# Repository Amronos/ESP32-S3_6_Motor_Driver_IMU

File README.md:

# ESP32-S3 6 Motor Driver with IMU

**_This board is currently in development._**

This board features an **ESP32-S3** microcontroller, a **6-channel** DC **motor driver**, and an integrated **BNO086 IMU** for precise motion and orientation data.<br>
It supports **encoder feedback**, enabling accurate position control. Motors can be driven at voltages up to **36V**.

This board is perfect for robots requiring more than two motors.<br>
Simply wire your motors, connect the board to a PC, another microcontroller, or even your phone/tablet and use the ESP32-S3's versatile communication options like I2C, SPI, UART, Wi-Fi, and Bluetooth to control your robot.

A full **Arduino library** for the board is available that allows you to control the motors, IMU, and read data from the encoders.<br>
Sample **ROS 2** packages are also available, that show the recommended usage of the board with ROS 2.

## 📂 About this Repository

This repository contains all code, design files, and information related to the ESP32-S3 6 Motor Driver with IMU.

### Directory Information

- [assets/](assets/): Assets used throughout this repository.
- [hardware_design/](hardware_design/): Complete KiCad project design files, schematic, 3D model, and BOM.

### Related Repositories

- [ESP32-S3_6_Motor_Driver_IMU_Library](https://github.com/amronos/ESP32-S3_6_Motor_Driver_IMU_Library/): Arduino library for the board.

## 📷 Images

## Costs

| Item                   | Price (USD) |
| ---------------------- | ----------- |
| Full PCB Manufacturing | $ 113.79    |
| Shipping               | $ 25        |
| **Subtotal**           | $ 138.79    |

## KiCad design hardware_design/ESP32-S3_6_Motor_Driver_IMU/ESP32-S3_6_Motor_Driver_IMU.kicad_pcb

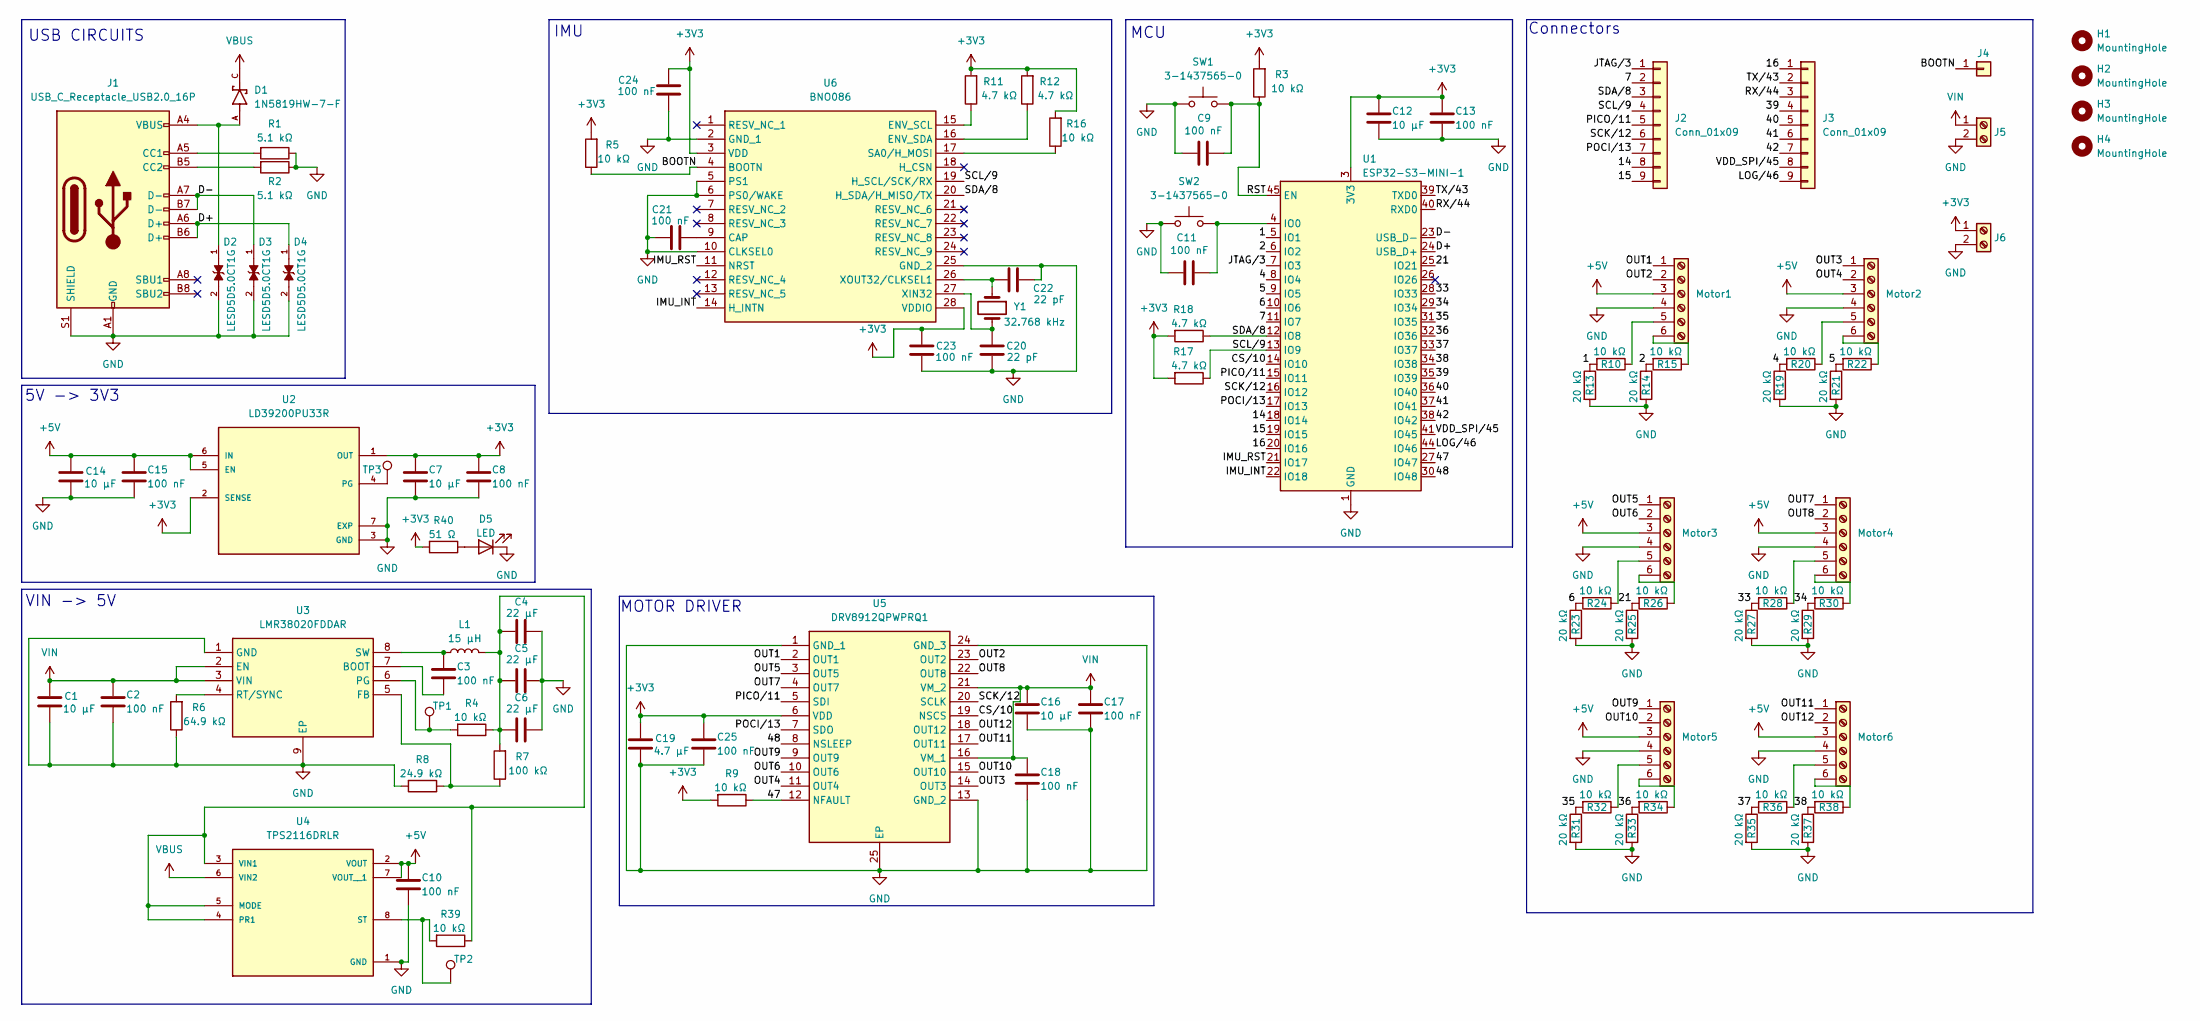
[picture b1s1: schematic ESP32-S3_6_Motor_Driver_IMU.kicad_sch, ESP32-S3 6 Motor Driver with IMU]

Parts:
C1, C16: 10 µF; C_0805_2012Metric
C2, C3, C8, C9, C10, C11, C13, C15, C17, C18, C21, C23, C24, C25: 100 nF; C_0402_1005Metric
C4, C5, C6: 22 µF; C_0603_1608Metric
C7, C12, C14: 10 µF; C_0603_1608Metric
C19: 4.7 µF; C_0402_1005Metric
C20, C22: 22 pF; C_0402_1005Metric
D1: 1N5819HW-7-F; SOD3715X145N
D2, D3, D4: LESD5D5.0CT1G; TVS_LESD5D5.0CT1G
D5: LED; LED_0603_1608Metric
H1, H2, H3, H4: MountingHole; MountingHole_3.2mm_M3
J1: USB_C_Receptacle_USB2.0_16P; USB_C_Receptacle_GCT_USB4105-xx-A_16P_TopMnt_Horizontal
J2, J3: Conn_01x09; PinHeader_1x09_P2.54mm_Vertical
J4: Conn_01x01; PinHeader_1x01_P2.54mm_Vertical
J5, J6: Screw_Terminal_01x02; TerminalBlock_Xinya_XY308-2.54-2P_1x02_P2.54mm_Horizontal
L1: 15 µH; INDPM102100X400N
Motor1, Motor2, Motor3, Motor4, Motor5, Motor6: Screw_Terminal_01x06; TerminalBlock_Xinya_XY308-2.54-6P_1x06_P2.54mm_Horizontal
R1, R2: 5.1 kΩ; R_0402_1005Metric
R3, R4, R5, R9, R10, R15, R16, R20, R22, R24, R26, R28, R30, R32, R34, R36, R38, R39: 10 kΩ; R_0402_1005Metric
R6: 64.9 kΩ; R_0402_1005Metric
R7: 100 kΩ; R_0402_1005Metric
R8: 24.9 kΩ; R_0402_1005Metric
R11, R12, R17, R18: 4.7 kΩ; R_0402_1005Metric
R13, R14, R19, R21, R23, R25, R27, R29, R31, R33, R35, R37: 20 kΩ; R_0402_1005Metric
R40: 51 Ω; R_0805_2012Metric
SW1, SW2: 3-1437565-0; SW_3-1437565-0
TP1, TP2, TP3: TestPoint; TestPoint_Pad_1.0x1.0mm
U1: ESP32-S3-MINI-1; ESP32-S2-MINI-1
U2: LD39200PU33R; SON95P300X300X100-7N
U3: LMR38020FDDAR; SOIC127P600X170-9N
U4: TPS2116DRLR; SOTFL50P160X60-8N
U5: DRV8912QPWPRQ1; SOP65P640X120-25N
U6: BNO086
Y1: 32.768 kHz; CM8V32768TA020125

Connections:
+3V3: C7.1, C8.1, C12.1, C13.1, C19.1, C23.1, C24.2, C25.1, J6.1, R3.2, R5.2, R9.2, R11.2, R12.2, R16.2, R17.2, R18.2, R40.2, U1.3 (3V3), U2.1 (OUT), U2.2 (SENSE), U5.6 (VDD), U6.3 (VDD), U6.28 (VDDIO)
+5V: C10.1, C14.1, C15.1, Motor1.3, Motor2.3, Motor3.3, Motor4.3, Motor5.3, Motor6.3, U2.5 (EN), U2.6 (IN), U4.2 (VOUT), U4.7 (VOUT__1)
/1: R10.2, R13.1, U1.5 (IO1)
/2: R14.1, R15.2, U1.6 (IO2)
/4: R19.1, R20.2, U1.8 (IO4)
/5: R21.1, R22.2, U1.9 (IO5)
/6: R23.1, R24.2, U1.10 (IO6)
/7: J2.2, U1.11 (IO7)
/14: J2.8, U1.18 (IO14)
/15: J2.9, U1.19 (IO15)
/16: J3.1, U1.20 (IO16)
/21: R25.1, R26.2, U1.25 (IO21)
/33: R27.1, R28.2, U1.28 (IO33)
/34: R29.1, R30.2, U1.29 (IO34)
/35: R31.1, R32.2, U1.31 (IO35)
/36: R33.1, R34.2, U1.32 (IO36)
/37: R35.1, R36.2, U1.33 (IO37)
/38: R37.1, R38.2, U1.34 (IO38)
/39: J3.4, U1.35 (IO39)
/40: J3.5, U1.36 (IO40)
/41: J3.6, U1.37 (IO41)
/42: J3.7, U1.38 (IO42)
/47: R9.1, U1.27 (IO47), U5.12 (NFAULT)
/48: U1.30 (IO48), U5.8 (NSLEEP)
/BOOTN: J4.1, R5.1, U6.4 (BOOTN)
/CS/10: U1.14 (IO10), U5.19 (NSCS)
/D+: D4.1, J1.A6 (D+), J1.B6 (D+), U1.24 (USB_D+)
/D-: D3.1, J1.A7 (D-), J1.B7 (D-), U1.23 (USB_D-)
/IMU_INT: U1.22 (IO18), U6.14 (H_INTN)
/IMU_RST: U1.21 (IO17), U6.11 (NRST)
/JTAG/3: J2.1, U1.7 (IO3)
/LOG/46: J3.9, U1.44 (IO46)
/OUT1: Motor1.1, U5.2 (OUT1)
/OUT2: Motor1.2, U5.23 (OUT2)
/OUT3: Motor2.1, U5.14 (OUT3)
/OUT4: Motor2.2, U5.11 (OUT4)
/OUT5: Motor3.1, U5.3 (OUT5)
/OUT6: Motor3.2, U5.10 (OUT6)
/OUT7: Motor4.1, U5.4 (OUT7)
/OUT8: Motor4.2, U5.22 (OUT8)
/OUT9: Motor5.1, U5.9 (OUT9)
/OUT10: Motor5.2, U5.15 (OUT10)
/OUT11: Motor6.1, U5.17 (OUT11)
/OUT12: Motor6.2, U5.18 (OUT12)
/PICO/11: J2.5, U1.15 (IO11), U5.5 (SDI)
/POCI/13: J2.7, U1.17 (IO13), U5.7 (SDO)
/RST: C9.2, R3.1, SW1.3 (B), SW1.4 (B), U1.45 (EN)
/RX/44: J3.3, U1.40 (RXD0)
/SCK/12: J2.6, U1.16 (IO12), U5.20 (SCLK)
/SCL/9: J2.4, R17.1, U1.13 (IO9), U6.19 (H_SCL/SCK/RX)
/SDA/8: J2.3, R18.1, U1.12 (IO8), U6.20 (H_SDA/H_MISO/TX)
/TX/43: J3.2, U1.39 (TXD0)
/VDD_SPI/45: J3.8, U1.41 (IO45)
GND: C1.2, C2.2, C4.2, C5.2, C6.2, C7.2, C8.2, C9.1, C10.2, C11.1, C12.2, C13.2, C14.2, C15.2, C16.2, C17.2, C18.2, C19.2, C20.2, C21.1, C22.2, C23.2, C24.1, C25.2, D2.2, D3.2, D4.2, D5.1 (K), J1.A1 (GND), J1.A12 (GND), J1.B1 (GND), J1.B12 (GND), J1.S1 (SHIELD), J5.2, J6.2, Motor1.4, Motor2.4, Motor3.4, Motor4.4, Motor5.4, Motor6.4, R1.1, R2.1, R6.1, R8.2, R13.2, R14.2, R19.2, R21.2, R23.2, R25.2, R27.2, R29.2, R31.2, R33.2, R35.2, R37.2, SW1.1 (A), SW1.2 (A), SW2.1 (A), SW2.2 (A), U1.1 (GND), U1.2 (GND), U1.42 (GND), U1.43 (GND), U1.46 (GND), U1.47 (GND), U1.48 (GND), U1.49 (GND), U1.50 (GND), U1.51 (GND), U1.52 (GND), U1.53 (GND), U1.54 (GND), U1.55 (GND), U1.56 (GND), U1.57 (GND), U1.58 (GND), U1.59 (GND), U1.60 (GND), U1.61 (GND), U1.62 (GND), U1.63 (GND), U1.64 (GND), U1.65 (GND), U2.3 (GND), U2.7 (EXP), U3.1 (GND), U3.9 (EP), U4.1 (GND), U5.1 (GND_1), U5.13 (GND_2), U5.24 (GND_3), U5.25 (EP), U6.2 (GND_1), U6.5 (PS1), U6.6 (PS0/WAKE), U6.10 (CLKSEL0), U6.25 (GND_2)
unnamed: D1.A, D2.1, J1.A4 (VBUS), J1.A9 (VBUS), J1.B4 (VBUS), J1.B9 (VBUS)
unnamed: D5.2 (A), R40.1
unnamed: J1.A5 (CC1), R1.2
unnamed: J1.B5 (CC2), R2.2
unnamed: Motor1.5, R10.1
unnamed: Motor1.6, R15.1
unnamed: Motor2.5, R20.1
unnamed: Motor2.6, R22.1
unnamed: Motor3.5, R24.1
unnamed: Motor3.6, R26.1
unnamed: Motor4.5, R28.1
unnamed: Motor4.6, R30.1
unnamed: Motor5.5, R32.1
unnamed: Motor5.6, R34.1
unnamed: Motor6.5, R36.1
unnamed: Motor6.6, R38.1
unnamed: C11.2, SW2.3 (B), SW2.4 (B), U1.4 (IO0)
unnamed: TP3.1, U2.4 (PG)
unnamed: C3.2, U3.7 (BOOT)
unnamed: R7.1, R8.1, U3.5 (FB)
unnamed: R4.2, TP1.1, U3.6 (PG)
unnamed: R6.2, U3.4 (RT/SYNC)
unnamed: C3.1, L1.1, U3.8 (SW)
unnamed: C4.1, C5.1, C6.1, L1.2, R4.1, R7.2, R39.1, U4.3 (VIN1), U4.4 (PR1), U4.5 (MODE)
unnamed: R39.2, TP2.1, U4.8 (ST)
unnamed: C21.2, U6.9 (CAP)
unnamed: R11.1, U6.15 (ENV_SCL)
unnamed: R12.1, U6.16 (ENV_SDA)
unnamed: R16.1, U6.17 (SA0/H_MOSI)
unnamed: C20.1, U6.27 (XIN32), Y1.2
unnamed: C22.1, U6.26 (XOUT32/CLKSEL1), Y1.1
VBUS: D1.C, U4.6 (VIN2)
VIN: C1.1, C2.1, C16.1, C17.1, C18.1, J5.1, U3.2 (EN), U3.3 (VIN), U5.16 (VM_1), U5.21 (VM_2)

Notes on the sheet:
MCU
USB CIRCUITS
Connectors
IMU
VIN -> 5V
5V -> 3V3
MOTOR DRIVER

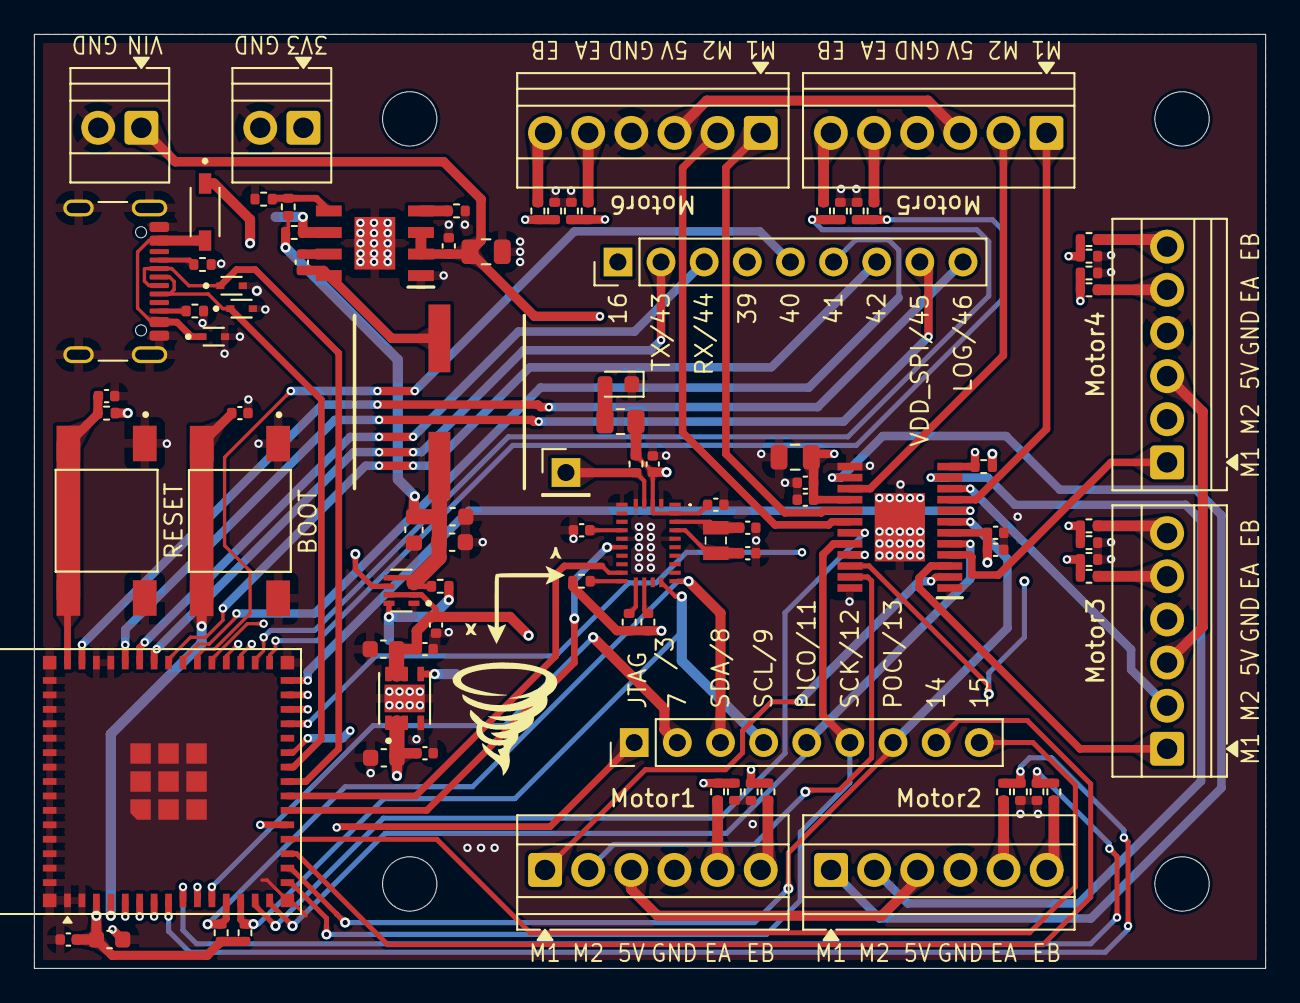
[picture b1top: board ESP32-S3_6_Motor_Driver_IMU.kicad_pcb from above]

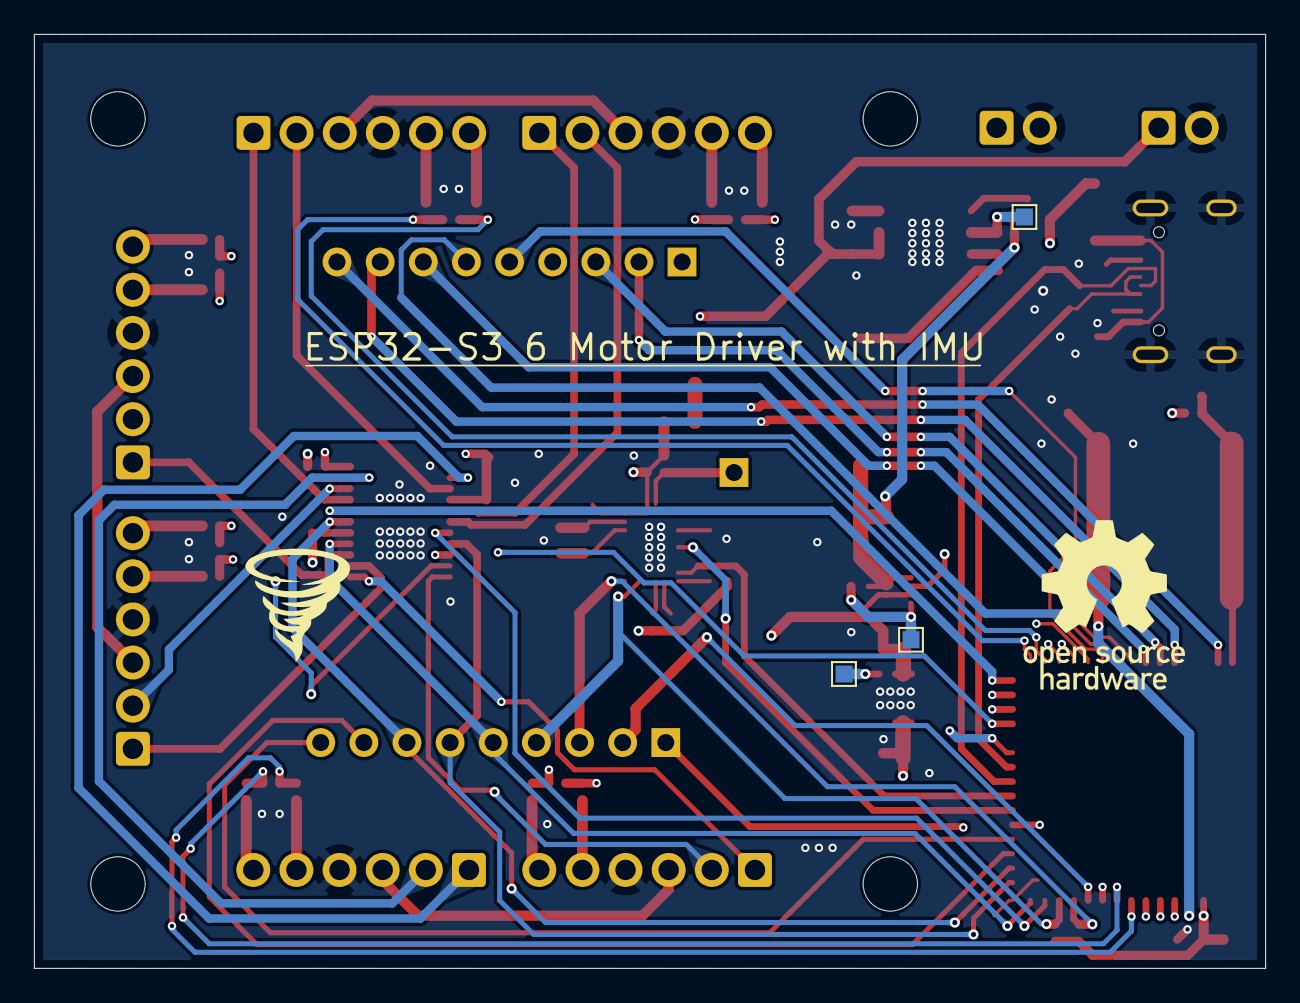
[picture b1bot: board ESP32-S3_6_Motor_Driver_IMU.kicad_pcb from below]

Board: 4 copper layers, 72.5 x 55.0 mm, 99 parts (3 on the bottom side), 87 nets.

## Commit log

2025-06-18 Complete schematic
2025-06-19 Add diagram showing ROS2 usage
    Also make fixes to schematic
2025-06-23 Complete PCB
2025-06-26 Make minor updates to the PCB
2025-06-26 Update README.md with more images
2025-06-27 Add costs to README.md
2025-06-28 Add more details to JOURNAL.md
2025-06-29 Move BOM.csv
